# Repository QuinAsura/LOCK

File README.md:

# LOCK

Localization, Obstacle avoidance , Control and Kinematics framework for differential steering systems.

# Introduction

* The Problem Statement assumes a static camera mounted with the complete view of the arena.
* The obstacles are assumed to be of a paticular predefined color.
* Uses A* for Path Planning with Erosion/Dilation to provide the bot with sufficient cleareance from obstacles.
* Controls written specifically for differential steering systems.

### Some Sample Tracks the bot successfully completed:

## Sample Tracks at NIT Pragyan:

## Sample Track at Kurukshetra:

Disclaimer: This is code developed specifically for competition and are certain to contain idiosyncrasies but it won in all
the competitions it participated (2015-2016) :)

# Competition Runs 1

# Competition Run 2

# Demo Run at Lab

####Tools needed
* USB HD webcam
* opencv 2.4.x
* Arduino UNO/MSP430
* HC06/Serial

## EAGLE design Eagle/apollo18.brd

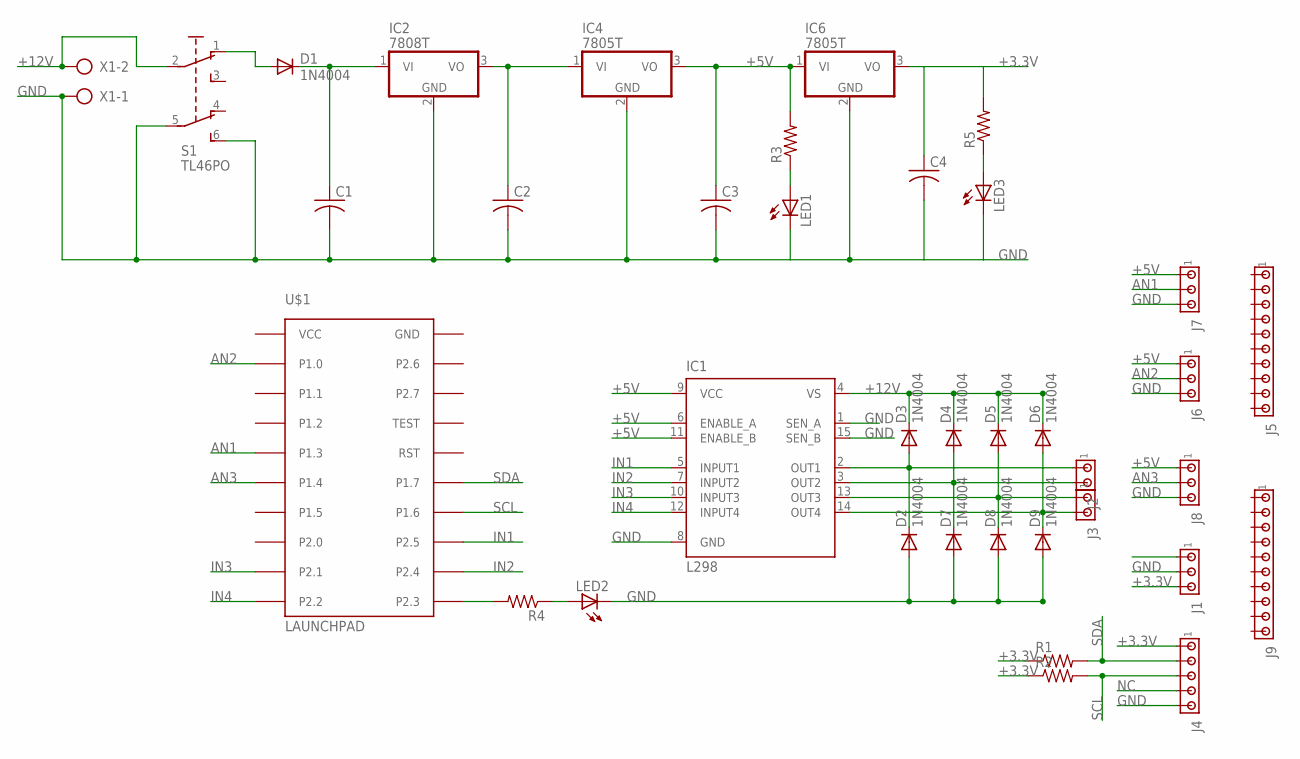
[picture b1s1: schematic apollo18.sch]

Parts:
C1, C2, C3: C-US025-050X050; C025-050X050
C4: C-US025-025X050; C025-025X050
D1, D2, D3, D4, D5, D6, D7, D8, D9: 1N4004; DO41-10
IC1: L298; MULTIWATT-15
IC2: 7808T; TO220H
IC4, IC6: 7805T; TO220H
J1, J6, J7, J8: MTA03-100; 10X03MTA
J2, J3: MTA02-100; 10X02MTA
J4: MTA05-100; 10X05MTA
J5, J9: MTA10-100; 10X10MTA
LED1, LED2, LED3: LED5MM
R1, R2, R3, R4, R5: R-US_0204/7; 0204/7
S1: TL46PO; TL4XPO
U$1: LAUNCHPAD
X1: AK300/2

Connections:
+3.3V: C4.1, IC6.3 (VO), J1.3, J4.1, R1.1, R2.1, R5.2
+5V: C3.1, IC1.6 (ENABLE_A), IC1.9 (VCC), IC1.11 (ENABLE_B), IC4.3 (VO), IC6.1 (VI), J6.1, J7.1, J8.1, R3.2
+12V: D3.C, D4.C, D5.C, D6.C, IC1.4 (VS), S1.2, X1.2
AN1: J7.2, U$1.P1.3
AN2: J6.2, U$1.P1.0
AN3: J8.2, U$1.P1.4
GND: C1.2, C2.2, C3.2, C4.2, D2.A, D7.A, D8.A, D9.A, IC1.1 (SEN_A), IC1.8 (GND), IC1.15 (SEN_B), IC2.2 (GND), IC4.2 (GND), IC6.2 (GND), J1.2, J4.5, J6.3, J7.3, J8.3, LED1.K (C), LED2.K (C), LED3.K (C), S1.5 (P1), S1.6 (S1), U$1.GND, X1.1
IN1: IC1.5 (INPUT1), U$1.P2.5
IN2: IC1.7 (INPUT2), U$1.P2.4
IN3: IC1.10 (INPUT3), U$1.P2.1
IN4: IC1.12 (INPUT4), U$1.P2.2
unnamed: D2.C, D3.A, IC1.2 (OUT1), J2.1
unnamed: D4.A, D7.C, IC1.3 (OUT2), J2.2
unnamed: D5.A, D8.C, IC1.13 (OUT3), J3.1
unnamed: D6.A, D9.C, IC1.14 (OUT4), J3.2
unnamed: C1.1, D1.C, IC2.1 (VI)
unnamed: D1.A, S1.1 (O)
unnamed: C2.1, IC2.3 (VO), IC4.1 (VI)
unnamed: LED3.A, R5.1
unnamed: LED1.A, R3.1
unnamed: R4.2, U$1.P2.3
unnamed: LED2.A, R4.1
NC: J4.4
SCL: J4.3, R2.2, U$1.P1.6
SDA: J4.2, R1.2, U$1.P1.7
VCC: U$1.VCC

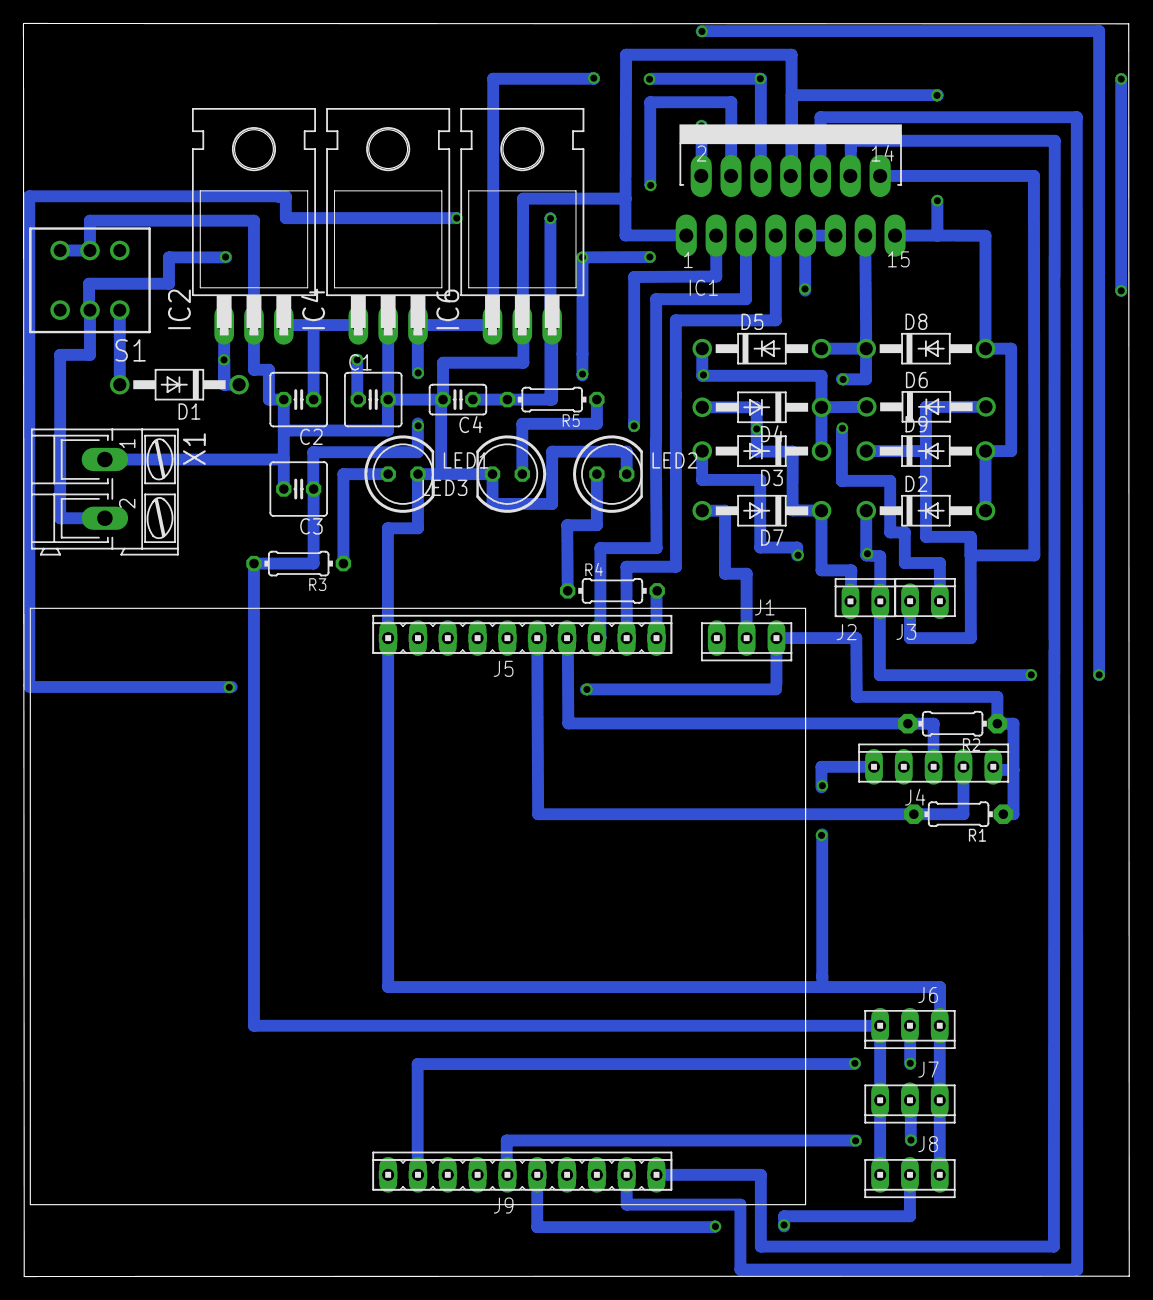
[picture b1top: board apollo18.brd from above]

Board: 2 copper layers, 94.2 x 106.7 mm, 37 parts (0 on the bottom side), 24 nets.

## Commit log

2015-08-03 1. Adding AI path planning 2. Dilation and Erosion for better understanding
2015-08-03 1. Added Kinematics class
2015-08-03 1. Added Localization based on contour 2. Added Thresholding code
2015-08-03 Adding sample file to find path
2015-08-06 Added licence
2015-08-07 Made changes to Licence file
2015-08-11 Added example for Localization
2015-08-17 Added complete Lock framework
2015-12-11 small typo
2016-01-31 Updated Readme for Arduino Xmas challenge
2016-11-13 Updated Videos
2016-12-11 updated readme removed tutorial
2016-12-11 updated proper paths
2016-12-11 minor changes and re-arrangement
2016-12-11 further re-arrangement
2016-12-11 Add License and authors
2016-12-31 Add Eagle CAD PCB files
2016-12-31 Update Eagle CAD PCB files
2017-01-05 Added weighted Astar
